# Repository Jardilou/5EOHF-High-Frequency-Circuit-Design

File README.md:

# 5EOHF-High-Frequency-Circuit-Design
The goal of this project is to create a pcb using an ESP32 microcontroller and able to send gps signals via LoRa communication. Two circuits will be fabricated separately, the first one for the microcontroller and the associated modules and the second one for the design of the antenna.

## 1. Project description
The components required for the main pcb assemply are listed in the BOM. Mainly, the modules are :
- GPS : SAM-M8Q-0
- ESP32 S3
- Lora Module RFM95 (868 MHz - without antenna, to be designed)
- Battery Power management 2S – BQ 25798
- USBC charging and programming pin
- SMA for custom antenna (868 MHz)

## 2. Schematic and Printed Circuit Board

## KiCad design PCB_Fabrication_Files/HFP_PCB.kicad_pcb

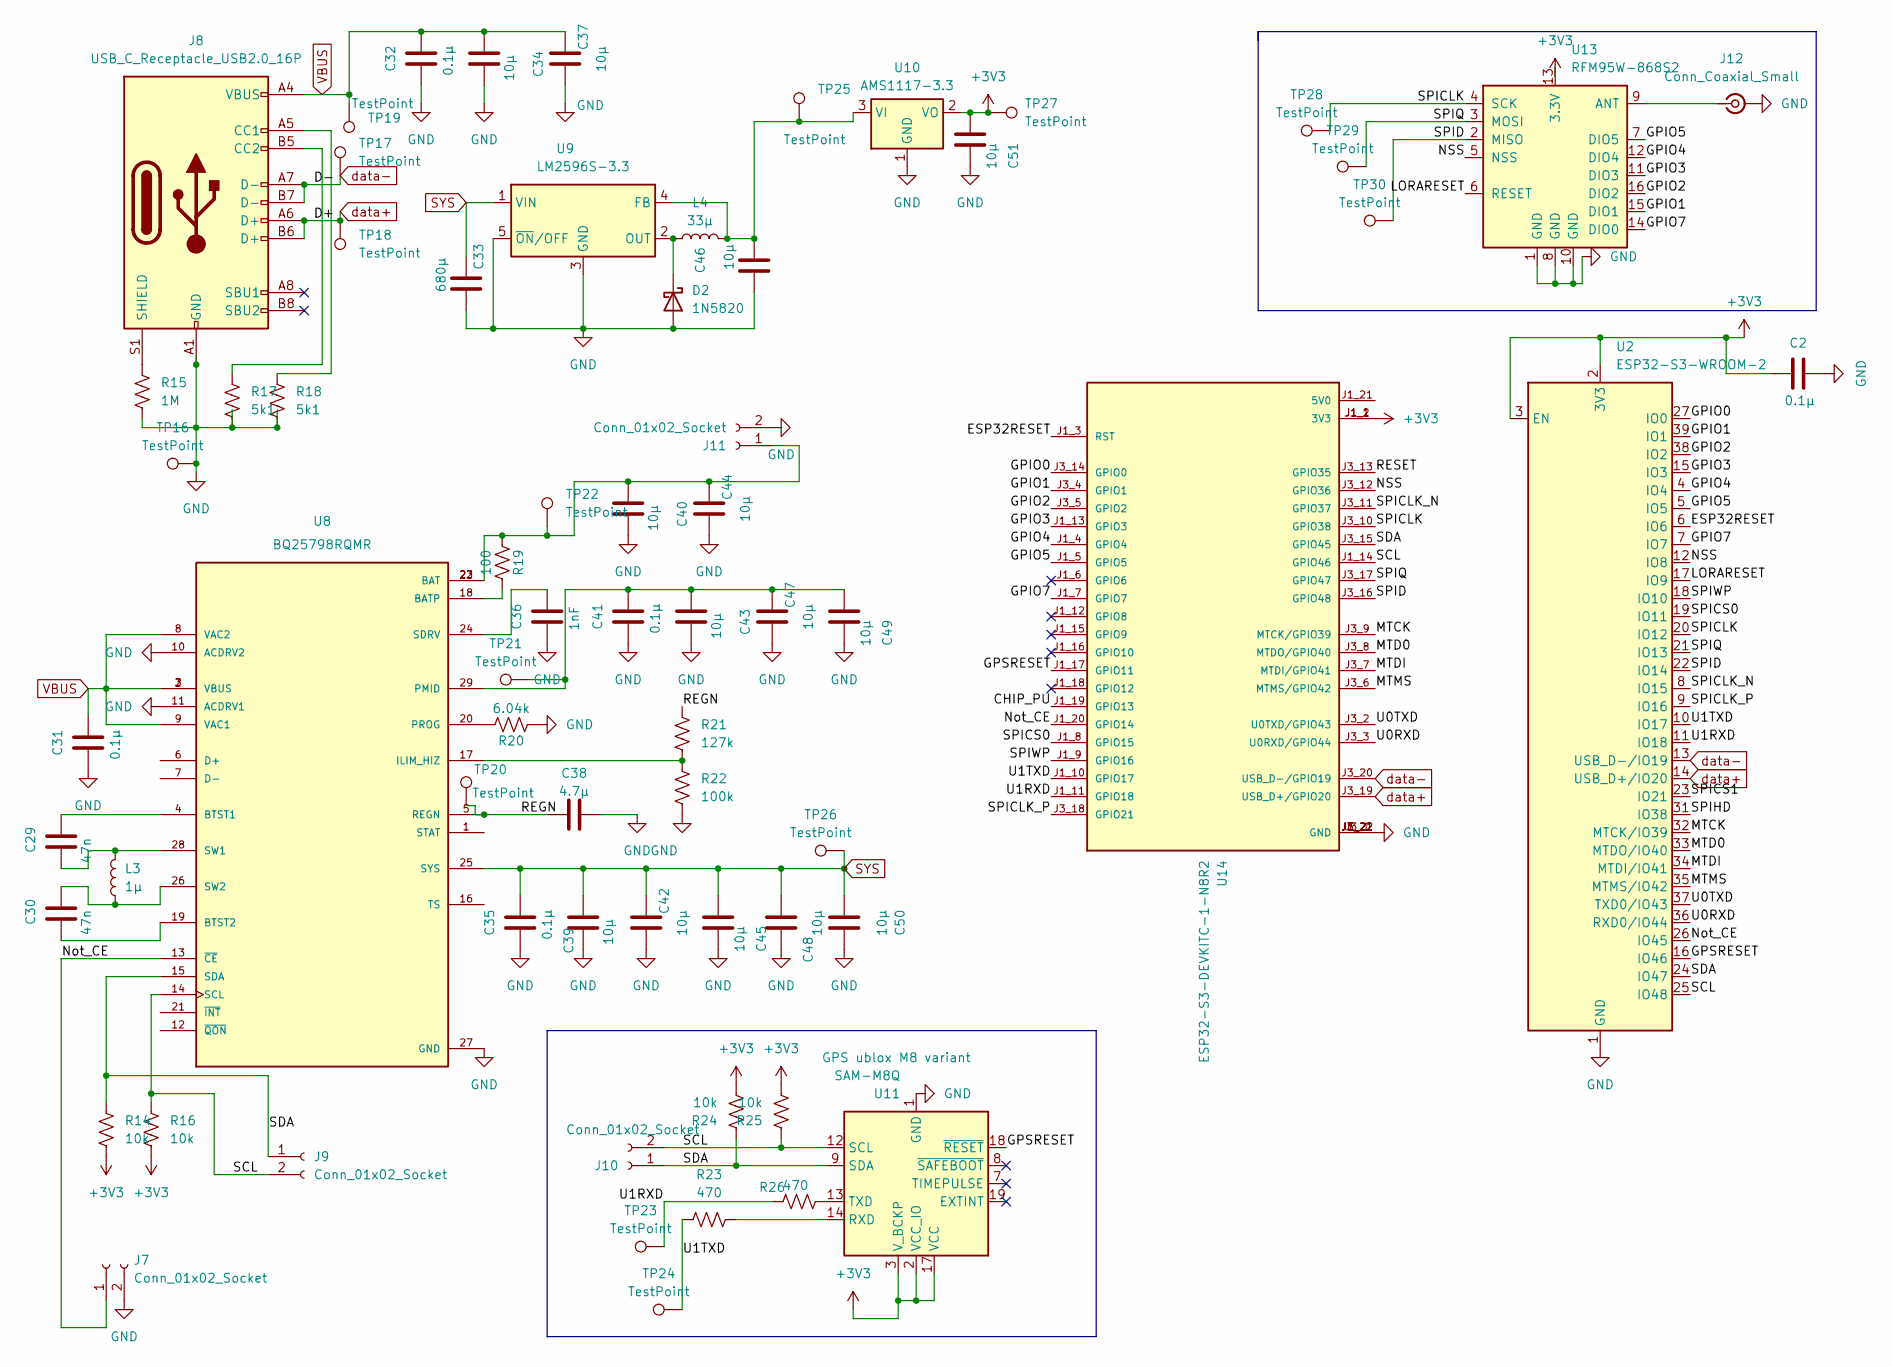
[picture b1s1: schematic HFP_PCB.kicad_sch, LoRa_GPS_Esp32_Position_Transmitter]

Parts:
C2, C31, C32, C35, C41: 0.1µ; C_0402_1005Metric
C29, C30: 47n; C_0603_1608Metric
C33: 680µ; CP_Elec_8x10
C34, C37, C39, C40, C42, C43, C44, C45, C46, C47, C48, C49, C50, C51: 10µ; C_1206_3216Metric
C36: 1nF; C_0402_1005Metric
C38: 4.7µ; C_0805_2012Metric
D2: 1N5820; D_DO-201AD_P15.24mm_Horizontal
J7, J9, J10, J11: Conn_01x02_Socket; JST_EH_B2B-EH-A_1x02_P2.50mm_Vertical
J8: USB_C_Receptacle_USB2.0_16P; USB_C_Receptacle_HRO_TYPE-C-31-M-12
J12: Conn_Coaxial_Small; BNC_TEConnectivity_1478204_Vertical
L3: 1µ; L_APV_ANR4018
L4: 33µ; L_APV_ANR8040
R14, R16, R24, R25: 10k; R_0201_0603Metric
R15: 1M; R_0201_0603Metric
R17, R18: 5k1; R_0201_0603Metric
R19: 100; R_0201_0603Metric
R20: 6.04k; R_0201_0603Metric
R21: 127k; R_0201_0603Metric
R22: 100k; R_0201_0603Metric
R23, R26: 470; R_0201_0603Metric
TP16, TP17, TP18, TP19, TP20, TP21, TP22, TP23, TP24, TP25, TP26, TP27, TP28, TP29, TP30: TestPoint; TestPoint_Keystone_5005-5009_Compact
U2: ESP32-S3-WROOM-2
U8: BQ25798RQMR; IC_BQ25798RQMR; PARTREV B
U9: LM2596S-3.3; TO-263-5_TabPin3
U10: AMS1117-3.3; SOT-223-3_TabPin2
U11: SAM-M8Q; ublox_SAM-M8Q
U13: RFM95W-868S2; HOPERF_RFM9XW_SMD
U14: ESP32-S3-DEVKITC-1-N8R2; XCVR_ESP32-S3-DEVKITC-1-N8R2; PARTREV V1

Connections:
+3V3: C2.1, C51.1, R14.1, R16.1, R24.1, R25.1, TP27.1, U2.2 (3V3), U2.3 (EN), U10.2 (VO), U11.2 (VCC_IO), U11.3 (V_BCKP), U11.17 (VCC), U13.13 (3.3V), U14.J1_1 (3V3), U14.J1_2 (3V3)
/CHIP_PU: U14.J1_19 (GPIO13)
/ESP32RESET: U2.6 (IO6), U14.J1_3 (RST)
/GPIO0: U2.27 (IO0), U14.J3_14 (GPIO0)
/GPIO1: U2.39 (IO1), U13.15 (DIO1), U14.J3_4 (GPIO1)
/GPIO2: U2.38 (IO2), U13.16 (DIO2), U14.J3_5 (GPIO2)
/GPIO3: U2.15 (IO3), U13.11 (DIO3), U14.J1_13 (GPIO3)
/GPIO4: U2.4 (IO4), U13.12 (DIO4), U14.J1_4 (GPIO4)
/GPIO5: U2.5 (IO5), U13.7 (DIO5), U14.J1_5 (GPIO5)
/GPIO7: U2.7 (IO7), U13.14 (DIO0), U14.J1_7 (GPIO7)
/GPSRESET: U2.16 (IO46), U11.18 (~RESET), U14.J1_17 (GPIO11)
/LORARESET: U2.17 (IO9), U13.6 (RESET)
/MTCK: U2.32 (MTCK/IO39), U14.J3_9 (MTCK/GPIO39)
/MTD0: U2.33 (MTDO/IO40), U14.J3_8 (MTDO/GPIO40)
/MTDI: U2.34 (MTDI/IO41), U14.J3_7 (MTDI/GPIO41)
/MTMS: U2.35 (MTMS/IO42), U14.J3_6 (MTMS/GPIO42)
/NSS: U2.12 (IO8), U13.5 (NSS), U14.J3_12 (GPIO36)
/Not_CE: J7.1, U2.26 (IO45), U8.13 (~CE), U14.J1_20 (GPIO14)
/REGN: C38.1, R21.1, TP20.1, U8.5 (REGN)
/RESET: U14.J3_13 (GPIO35)
/SCL: J9.2, J10.2, R16.2, R25.2, U2.25 (IO48), U8.14 (SCL), U11.12 (SCL), U14.J1_14 (GPIO46)
/SDA: J9.1, J10.1, R14.2, R24.2, U2.24 (IO47), U8.15 (SDA), U11.9 (SDA), U14.J3_15 (GPIO45)
/SPICLK: TP28.1, U2.20 (IO12), U13.4 (SCK), U14.J3_10 (GPIO38)
/SPICLK_N: U2.8 (IO15), U14.J3_11 (GPIO37)
/SPICLK_P: U2.9 (IO16), U14.J3_18 (GPIO21)
/SPICS0: U2.19 (IO11), U14.J1_8 (GPIO15)
/SPICS1: U2.23 (IO21)
/SPID: TP30.1, U2.22 (IO14), U13.2 (MISO), U14.J3_16 (GPIO48)
/SPIHD: U2.31 (IO38)
/SPIQ: TP29.1, U2.21 (IO13), U13.3 (MOSI), U14.J3_17 (GPIO47)
/SPIWP: U2.18 (IO10), U14.J1_9 (GPIO16)
/U0RXD: U2.36 (RXD0/IO44), U14.J3_3 (U0RXD/GPIO44)
/U0TXD: U2.37 (TXD0/IO43), U14.J3_2 (U0TXD/GPIO43)
/U1RXD: R26.1, TP23.1, U2.11 (IO18), U14.J1_11 (GPIO18)
/U1TXD: R23.1, TP24.1, U2.10 (IO17), U14.J1_10 (GPIO17)
GND: C2.2, C31.2, C32.2, C33.1, C34.2, C35.2, C36.2, C37.2, C38.2, C39.2, C40.2, C41.2, C42.2, C43.2, C44.2, C45.2, C46.1, C47.2, C48.2, C49.2, C50.2, C51.2, D2.2 (A), J7.2, J8.A1 (GND), J8.A12 (GND), J8.B1 (GND), J8.B12 (GND), J11.2, J12.2 (Ext), R15.1, R17.1, R18.1, R20.1, R22.2, TP16.1, U2.1 (GND), U2.40 (GND), U2.41 (GND), U8.10 (ACDRV2), U8.11 (ACDRV1), U8.27 (GND), U9.3 (GND), U9.5 (~ON/OFF), U10.1 (GND), U11.1 (GND), U11.4 (GND), U11.5 (GND), U11.6 (GND), U11.10 (GND), U11.11 (GND), U11.15 (GND), U11.16 (GND), U11.20 (GND), U13.1 (GND), U13.8 (GND), U13.10 (GND), U14.J1_22 (GND), U14.J3_1 (GND), U14.J3_21 (GND), U14.J3_22 (GND)
unnamed: D2.1 (K), L4.1, U9.2 (OUT)
unnamed: J8.A5 (CC1), R18.2
unnamed: J8.B5 (CC2), R17.2
unnamed: J8.S1 (SHIELD), R15.2
unnamed: C40.1, C44.1, J11.1, R19.1, TP22.1, U8.22 (BAT), U8.23 (BAT)
unnamed: J12.1 (In), U13.9 (ANT)
unnamed: R19.2, U8.18 (BATP)
unnamed: C29.1, U8.4 (BTST1)
unnamed: C30.2, U8.19 (BTST2)
unnamed: R21.2, R22.1, U8.17 (ILIM_HIZ)
unnamed: C41.1, C43.1, C47.1, C49.1, TP21.1, U8.29 (PMID)
unnamed: R20.2, U8.20 (PROG)
unnamed: C36.1, U8.24 (SDRV)
unnamed: C29.2, L3.2, U8.28 (SW1)
unnamed: C30.1, L3.1, U8.26 (SW2)
unnamed: C46.2, L4.2, TP25.1, U9.4 (FB), U10.3 (VI)
unnamed: R23.2, U11.14 (RXD)
unnamed: R26.2, U11.13 (TXD)
SYS: C33.2, C35.1, C39.1, C42.1, C45.1, C48.1, C50.1, TP26.1, U8.25 (SYS), U9.1 (VIN)
VBUS: C31.1, C32.1, C34.1, C37.1, J8.A4 (VBUS), J8.A9 (VBUS), J8.B4 (VBUS), J8.B9 (VBUS), TP19.1, U8.2 (VBUS), U8.3 (VBUS), U8.8 (VAC2), U8.9 (VAC1)
data+: J8.A6 (D+), J8.B6 (D+), TP18.1, U2.14 (USB_D+/IO20), U14.J3_19 (USB_D+/GPIO20)
data-: J8.A7 (D-), J8.B7 (D-), TP17.1, U2.13 (USB_D-/IO19), U14.J3_20 (USB_D-/GPIO19)

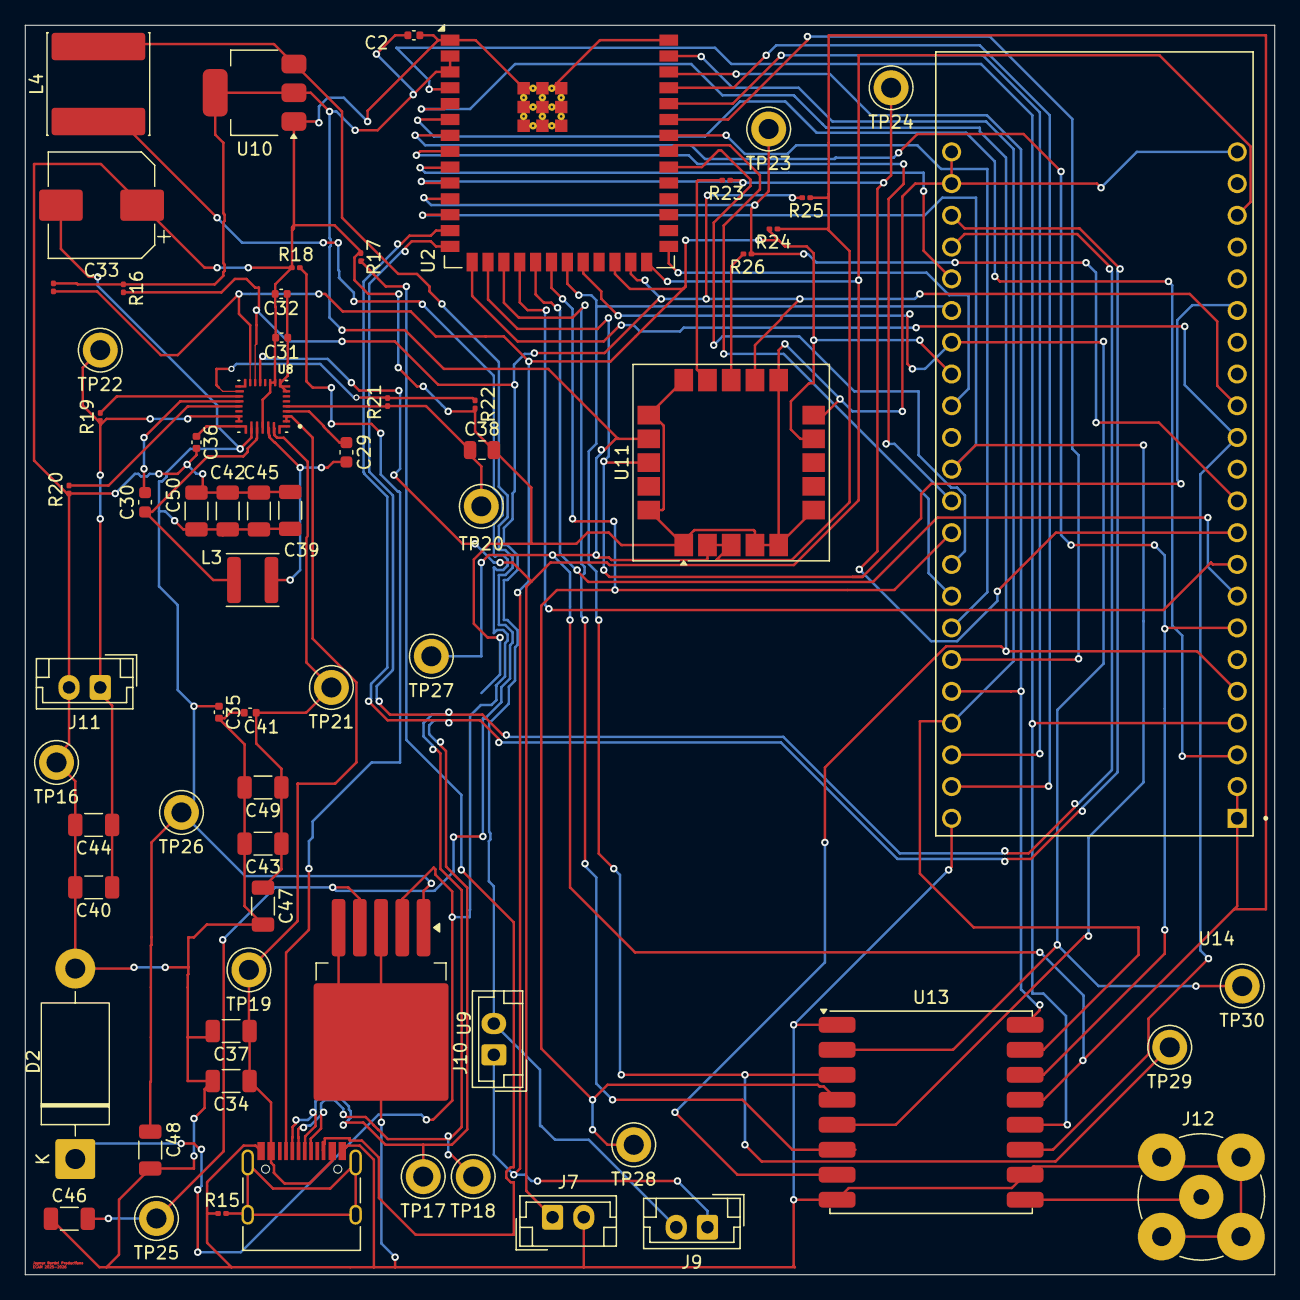
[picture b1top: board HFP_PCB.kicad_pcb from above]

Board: 2 copper layers, 100.0 x 100.0 mm, 68 parts (1 on the bottom side), 54 nets.

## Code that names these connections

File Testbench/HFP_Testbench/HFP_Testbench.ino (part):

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  - SAM-M8Q: UART NMEA reader + I2C presence probe (addr 0x42)
  - RFM95: SPI RegVersion read, Reset cycle, optional LoRa transmit (if "LoRa" library is installed)
  - Serial output at 115200 for results
  IMPORTANT: Many ESP32 boards reserve GPIO6..GPIO11 for flash/PSRAM. Using GPIO6/GPIO7 may break the module.
  We should adjust pins if we encounter boot issues!
*/

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
///// USER PIN CONFIG (from your message) /////
const int PIN_RFM95_SCK  = 33; // SCK
const int PIN_RFM95_SPIQ = 34; // SPIQ (may be DIO/IRQ depending on your board)
const int PIN_RFM95_SPID = 35; // SPID (MISO/MOSI naming ambiguous; treat as MISO here)
const int PIN_RFM95_NSS  = 6;  // NSS (WARNING: GPIO6 is sometimes reserved for flash)
const int PIN_RFM95_RESET= 7;  // RESET (WARNING: GPIO7 may be reserved)
const int PIN_RFM95_DIO0 = PIN_RFM95_SPIQ; // fallback: if SPIQ is DIO0/IRQ, used for LoRa library

const int GPS_UART_TX = 17; // U1TXD (ESP32 -> GPS)
const int GPS_UART_RX = 18; // U1RXD (GPS -> ESP32)
const int GPS_I2C_SDA = 51; // GPIO45
const int GPS_I2C_SCL = 52; // GPIO46
const uint8_t GPS_I2C_ADDR = 0x42; // typical UBX I2C address (0x42)

const int LED_TEST_PIN = 2; // on-board LED or any test pin
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  printHeader("RFM95 SPI Basic Test");
  Serial.println("Configuring HSPI with user pins and toggling reset.");
  // configure HSPI pins
  // NOTE: If your board uses GPIO6/GPIO7 for flash, this will break. Consider changing NSS/RESET.
  hspi.begin(PIN_RFM95_SCK, PIN_RFM95_SPID, /*MOSI*/ PIN_RFM95_SCK, /*SCLK duplicated*/ PIN_RFM95_SCK); 
  // The above line won't be perfect for some boards — we still set pinMode for NSS
  pinMode(PIN_RFM95_NSS, OUTPUT);
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
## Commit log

2025-11-18 Create init
2025-11-18 Create PCB_Fabrication_Files
2025-11-26 code antenne
